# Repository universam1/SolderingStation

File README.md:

# SolderingStation

Schematics and Code for a DIY Weller RT soldering station.

Find original idea at https://debugginglab.wordpress.com/2014/10/30/soldering-station/

## Additions

- Calculating Power usage by measuring the input voltage
- Limit Power dynamically, displaying it
- allowing different voltage PSUs
- more UI changes
- more convenient Poti mappings
- introducing serial command to configure (more to do)

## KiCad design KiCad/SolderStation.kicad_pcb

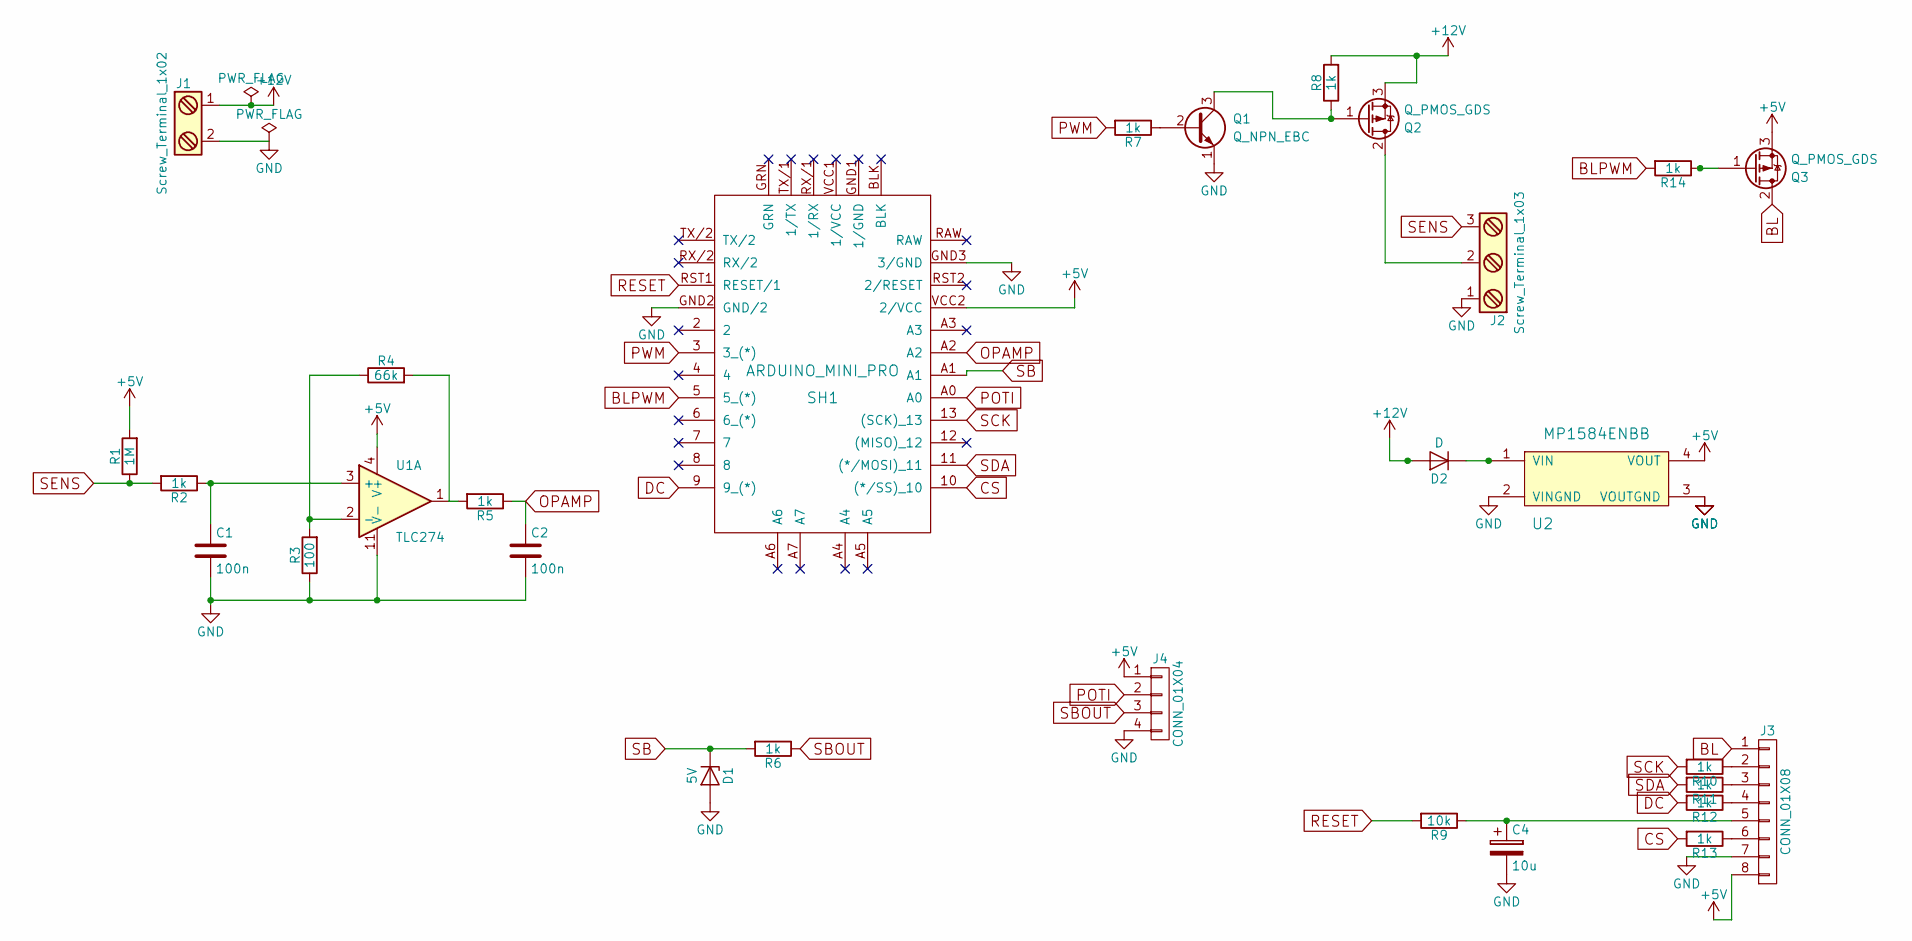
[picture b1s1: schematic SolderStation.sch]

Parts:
C1, C2: 100n; C_Disc_D5.0mm_W2.5mm_P2.50mm
C4: 10u; CP_Radial_D7.5mm_P2.50mm
D1: 5V; D_DO-15_P5.08mm_Vertical_AnodeUp
D2: D; D_DO-15_P5.08mm_Vertical_AnodeUp
J1: Screw_Terminal_1x02; bornier2
J2: Screw_Terminal_1x03; bornier3
J3: CONN_01X08; Pin_Header_Straight_1x08_Pitch2.54mm
J4: CONN_01X04; Pin_Header_Straight_1x04_Pitch2.54mm
Q1: Q_NPN_EBC; TO-92_Molded_Wide
Q2: Q_PMOS_GDS; TO-220_Vertical
Q3: Q_PMOS_GDS; SOT-23_Handsoldering
R1: 1M; R_Axial_DIN0207_L6.3mm_D2.5mm_P7.62mm_Horizontal
R2, R5, R6, R7, R8, R10, R11, R12, R13, R14: 1k; R_Axial_DIN0207_L6.3mm_D2.5mm_P7.62mm_Horizontal
R3: 100; R_Axial_DIN0207_L6.3mm_D2.5mm_P7.62mm_Horizontal
R4: 66k; R_Axial_DIN0207_L6.3mm_D2.5mm_P7.62mm_Horizontal
R9: 10k; R_Axial_DIN0207_L6.3mm_D2.5mm_P7.62mm_Horizontal
SH1: ARDUINO_MINI_PRO; ARDUINO_MINI_PRO_V10
U1: TLC274; DIP-14_W7.62mm_Socket_LongPads
U2: MP1584ENBB; MP1584_buck_module

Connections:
+5V: J3.8, J4.1, Q3.3 (S), R1.2, SH1.VCC2 (2/VCC), U1.4 (V+), U2.4 (VOUT)
+12V: D2.2 (A), J1.1, Q2.3 (S), R8.2
BL: J3.1, Q3.2 (D)
BLPWM: R14.2, SH1.5 (5_(*))
CS: R13.2, SH1.10 ((*/SS)_10)
DC: R12.2, SH1.9 (9_(*))
GND: C1.2, C2.2, C4.2, D1.2 (A), J1.2, J2.1, J3.7, J4.4, Q1.1 (E), R3.1, SH1.GND2 (GND/2), SH1.GND3 (3/GND), U1.11 (V-), U2.2 (VINGND), U2.3 (VOUTGND)
unnamed: C1.1, R2.1, U1.3 (+)
unnamed: C4.1, J3.5, R9.1
unnamed: D2.1 (K), U2.1 (VIN)
unnamed: J2.2, Q2.2 (D)
unnamed: J3.2, R10.1
unnamed: J3.3, R11.1
unnamed: J3.4, R12.1
unnamed: J3.6, R13.1
unnamed: Q1.2 (B), R7.1
unnamed: Q1.3 (C), Q2.1 (G), R8.1
unnamed: Q3.1 (G), R14.1
unnamed: R3.2, R4.1, U1.2 (-)
unnamed: R4.2, R5.2, U1.1
OPAMP: C2.1, R5.1, SH1.A2
POTI: J4.2, SH1.A0
PWM: R7.2, SH1.3 (3_(*))
RESET: R9.2, SH1.RST1 (RESET/1)
SB: D1.1 (K), R6.2, SH1.A1
SBOUT: J4.3, R6.1
SCK: R10.2, SH1.13 ((SCK)_13)
SDA: R11.2, SH1.11 ((*/MOSI)_11)
SENS: J2.3, R1.1, R2.2

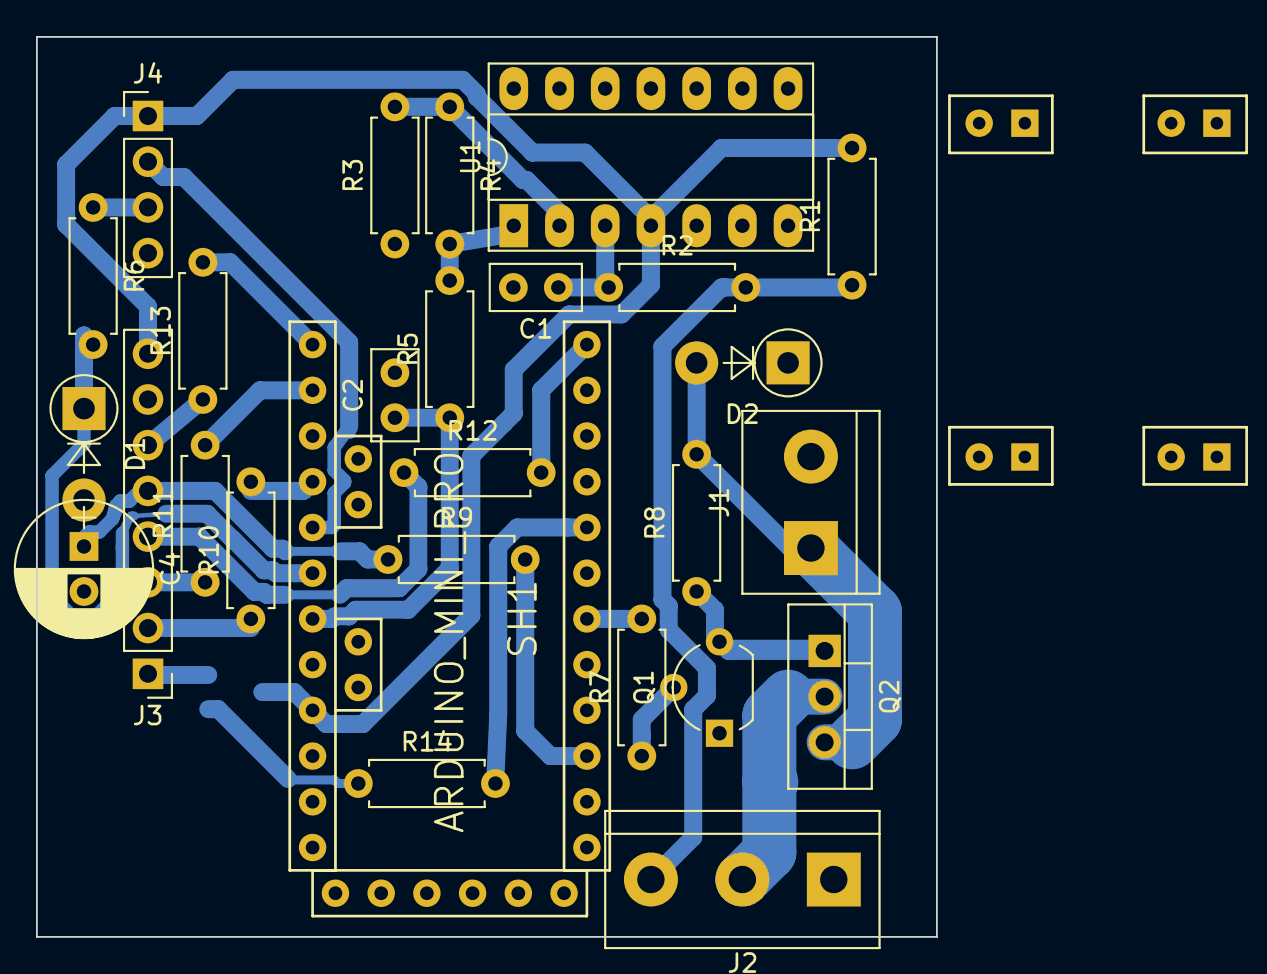
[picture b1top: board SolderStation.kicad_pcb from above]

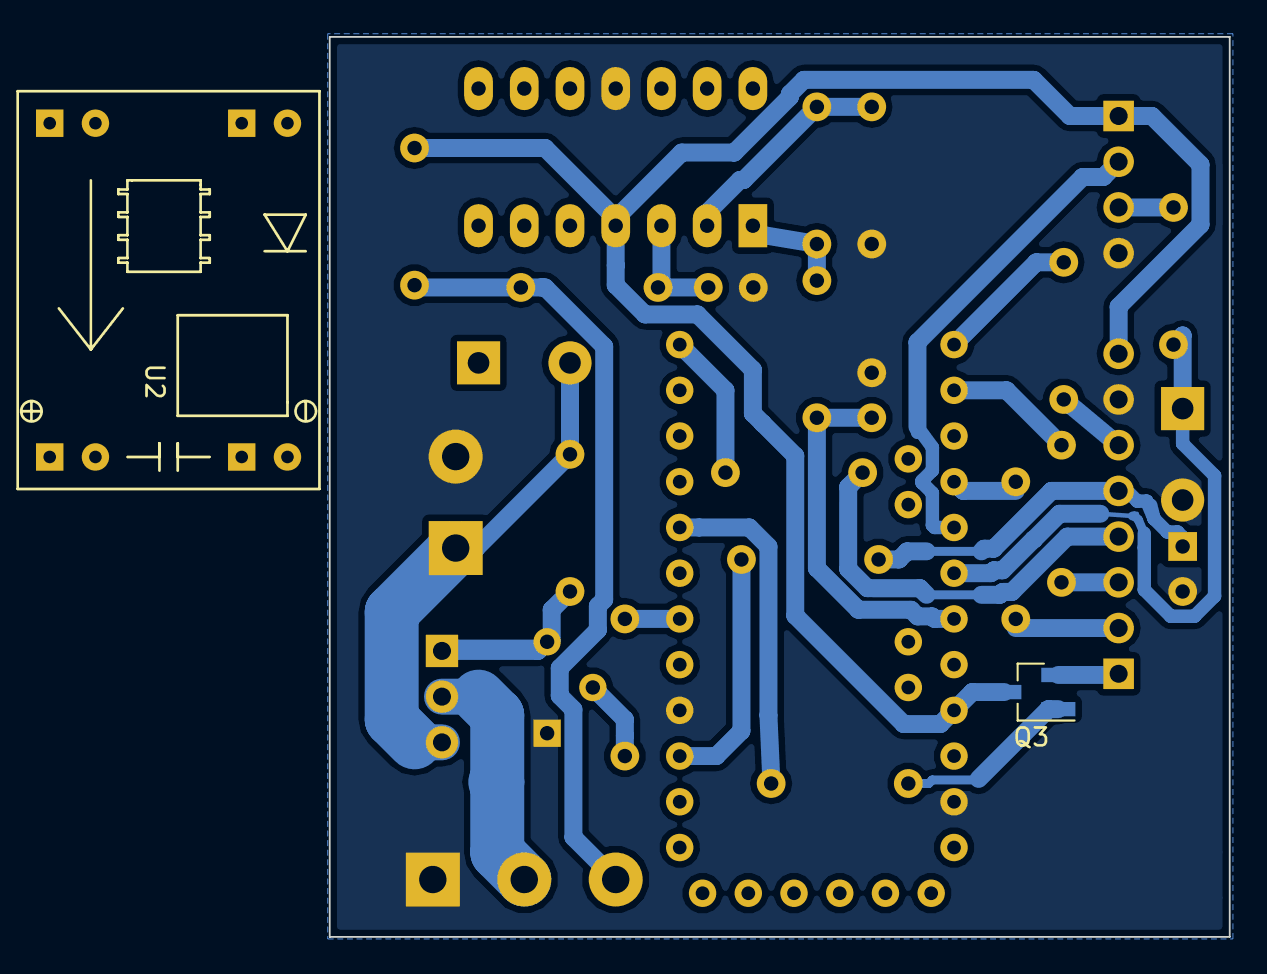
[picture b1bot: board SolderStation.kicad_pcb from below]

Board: 2 copper layers, 50.0 x 50.0 mm, 29 parts (2 on the bottom side), 29 nets.

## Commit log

2016-04-24 Textposition angepasst.
2016-05-22 backlight pin, Anzeige beruhigt und Farbübergang
    pin 5 ist direkt an BL angeschlossen
    pin 7 auch aber verstärkt über einen Transistor
    pin 5 wurde als Eingang eingestellt und statt dessen wird pin 7 für die
    Hintergrundbeleuchtung verwendet
    Die Farbübergänge waren nicht einstellbar und stellenweise zu dunkel.
    Sie sind jetzt immer gleich hell und die Temperaturabstände sind
2016-05-22 README aktualisiert
2016-05-22 utf8 for README
2016-05-22 README
    # Conflicts:
    # README.md
2016-05-28 PWM-Balken und AutoOff nach 10min
2016-06-26 3d bottom mod + handle
2017-06-27 PlatformIO init
2017-06-28 UI improvemtens
2017-06-28 adc calibration
2017-06-30 Hand
